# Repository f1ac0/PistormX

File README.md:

# Pistorm'X
If you don't know about Pistorm, the MC68000 CPU replacement using a raspberry Pi, see here : https://github.com/captain-amygdala/pistorm

This PiStorm'X is a simplified CPU board, where all the logic is integrated inside a single CPLD with 5V compatible IOs.

The "Alpha" directory contains the PCB design and CPLD logic files for the first design of the Amiga 500 board and possible mods.

The "Beta" directory shares a second generation of boards for the Amiga 500, Amiga 600 and Amiga 1200. To enjoy both the speed of the PiStorm and the compatibility of the original hardware, they include the ability to disable the Pi and run the original 68k CPU, and the A500 and A600 ones also add 2MB of autoconfig Fast RAM.

Please read the README files there for more info.

# Experimental status
These boards are still experimental, not well tested, and might not work with all system revisions and Pi or 68k software nor provide the same performance or feature than the original. That it works for me does not mean that it will work for you. For this reason you are welcome to assemble your own and share test reports in the discord channel named "beta-testing-pistormx". And for this same reason this board or derivatives must not be sold to end users : do not sell it and do not buy it yet.

- I am an end user, where can I buy it? Buy one of the original PiStorm CPU boards.
- I am a builder, can I sell it? For now, please test it and report your test results.
- I am a maker, can I build derivatives? For now, please test it and report your test results.

# Acknowledgements
The board and its firmware are inspired by the original Pistorm : https://github.com/captain-amygdala/pistorm.
I would like to thank Claude Schwarz for designing and open sourcing the Pistorm and for letting other projects like this one use the name and get inspired by the source code.
Thank you also to EDU_ARANA for letting me use his Pistorm logo with some modifications on the PCB silkscreen.
It is not supported by the PiStorm developers, please don't bother them with issues you might have with it.

# Disclaimer
This is a hobbyist project, it comes with no warranty and no support. Also remember that the Amiga machines are about 30 years old and may fail because of such hardware expansions. Use with caution it could burn your Pi, your Amiga, your house.

I publish my work under the CC-BY-NC-SA license. You may build a board for you or your friend but will not sell or buy it commercially because it is experimental. You must keep the original author's name, source repository (https://github.com/f1ac0/PistormX) and licensing conditions even if you modify the product.

If you find it useful and want to reward my hard work : I am always looking for Amiga/Amstrad CPC and such retro hardware to repair and hack, or software licenses for these. Other than that, give to charities and reduce your carbon footprint.

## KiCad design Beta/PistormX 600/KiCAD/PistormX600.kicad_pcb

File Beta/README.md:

# PiStorm'X Work in progress

NOT ALL DESIGNS IN THIS DIRECTORY ARE TESTED.

If you don't know about PiStorm, the MC68000 CPU replacement using a raspberry Pi, see here : https://github.com/captain-amygdala/pistorm. This PiStorm'X is a simplified CPU board, where all the logic is integrated inside a single CPLD.

# Experimental status
These boards are either experimental, not finished, not yet tested, and might not work for you, have bugs with some system revisions and Pi or 68k software, or have less performance or feature than the original. For this reason you will find here source files only, not fabrication files or ready to use binaries. If you have enough development skills to use them and know what you are doing, you may assemble your own and share test reports in the discord channel named "beta-testing-pistormx". And for this same reason these boards or derivatives must not be sold to end users.

I publish my work under the CC-BY-NC-SA license. You may build a board for you but will not sell or buy it commercially because it is experimental. You must keep the original author's name, source repository (https://github.com/f1ac0/PistormX) and licensing conditions even if you modify the product.

If you find it useful and want to reward my hard work : I am always looking for Amiga/Amstrad CPC/C64 and such retro hardware to repair and hack, or software licenses for these. Other than that, please give to charities and reduce your carbon footprint.

# Acknowledgements
The board and its firmware are inspired by the original PiStorm : https://github.com/captain-amygdala/pistorm.
I would like to thank Claude Schwarz for designing and open sourcing the PiStorm and for letting other projects like this one use the name and get inspired by the source code.
Thank you also to EDU_ARANA for letting me use his PiStorm logo with some modifications on the PCB silkscreen.
It is not supported by the PiStorm developers, please don't bother them with issues you might have with it.

# PiStorm'X 500
The original PiStorm'X project for the Amiga 500 was shared in February 2022. In November 2022, I published the PiStorm'X-68k, a modification to the original project that allow keeping and using the original 68000 by deactivating the PiStorm when needed using a long reset.

This PiStorm'X 500 is an updated board for the Amiga 500 :
- including the PiStorm'X-68k modifications,
- moving the Pi away from the 68000, over the A500 ROM, in order to improve thermal repartition,
- adding 2MB of Fast RAM, which is useful especially during 68000 operation when the Pi is disabled : there was enough room on the two sided board and I believe it is a nice addition to the stock Amiga 500.

/!\ This 1.0 revision board need a patch wire between pin 15 of the 68k header to the pad marked OVR /!\ Do not connect anything else to this pad and check that the BGACK solder jumper is not shorted to the BGACK pin. /!\

The development of this board has been painful. I killed the 7805 Super Fat Agnus of my Rev8a in the development process, because of a dodgy home designed and printed ZIF64 socket that doesn't lock correctly, and an idiot operator that touched the pins without ESD protection. I am looking for an affordable replacement. Then I fought a timing problem caused by the slow transition on the 7MHz clock, because I thought it was a good idea to route it to a global clock pin of the CPLD. It was not - see https://support.xilinx.com/s/article/3226, on the Rev6 with Agnus 8372 318069-02 they are about 25ns, compared to 10ns on my A600 Rev1.5 with Agnus 8375 318069-10 - and this is the reason for the patch wire.

This board is actually working on my A500 Rev6.

# PiStorm'X 600
The PiStorm'X 600 brings the same features as the PiStorm'X 500 to the Amiga 600 : maintain reset during 6 seconds or more to use the 68000, and benefit of 2MB of Fast RAM.

This board is actually working on my A600.

# PiStorm'X 1K2
I have heard about the PiStorm32 for the Amiga 1200 and I wanted to make my own in the Pistorm'X way.

This is not yet finished and untested.

- There are two board layouts : the first board steals the component placement form the PiStorm32-lite ; the second "alt" one offers a more "traditional" design to access the Pi in the trapdoor. Both boards share the same logic but have different CPLD pinout and so will require different bitstreams. With the latter if you don't mind leaving the trapdoor open you may install a standard pin header for the Pi GPIO, leaving the A1200 edge connector as the only special part.
- Since it needs to cope with 32 bits operation with misaligned addresses and dynamic bus sizing, it requires a larger XC95288 CPLD, both in pin count and macrocells.
- This added logic must still be full of bugs and may never work.
- I reused the Pi pinouts from the Pistorm32-lite and since it does not have room for the jtag anymore, the device needs to be programmed externally.
- Even with the same Pi pinouts, it will need updated emulators that does not try to program a FPGA at power up : I hope this will be possible to deactivate it in future upstream releases.
- Like the original PiStorm'X that is not limited by external buffers, it might also be possible to use a faster protocol to speed up chip access a little bit. Or offload some complexity to the emulator to fit inside an even smaller/cheaper CPLD.

For sure this will need some more effort to first make it work !

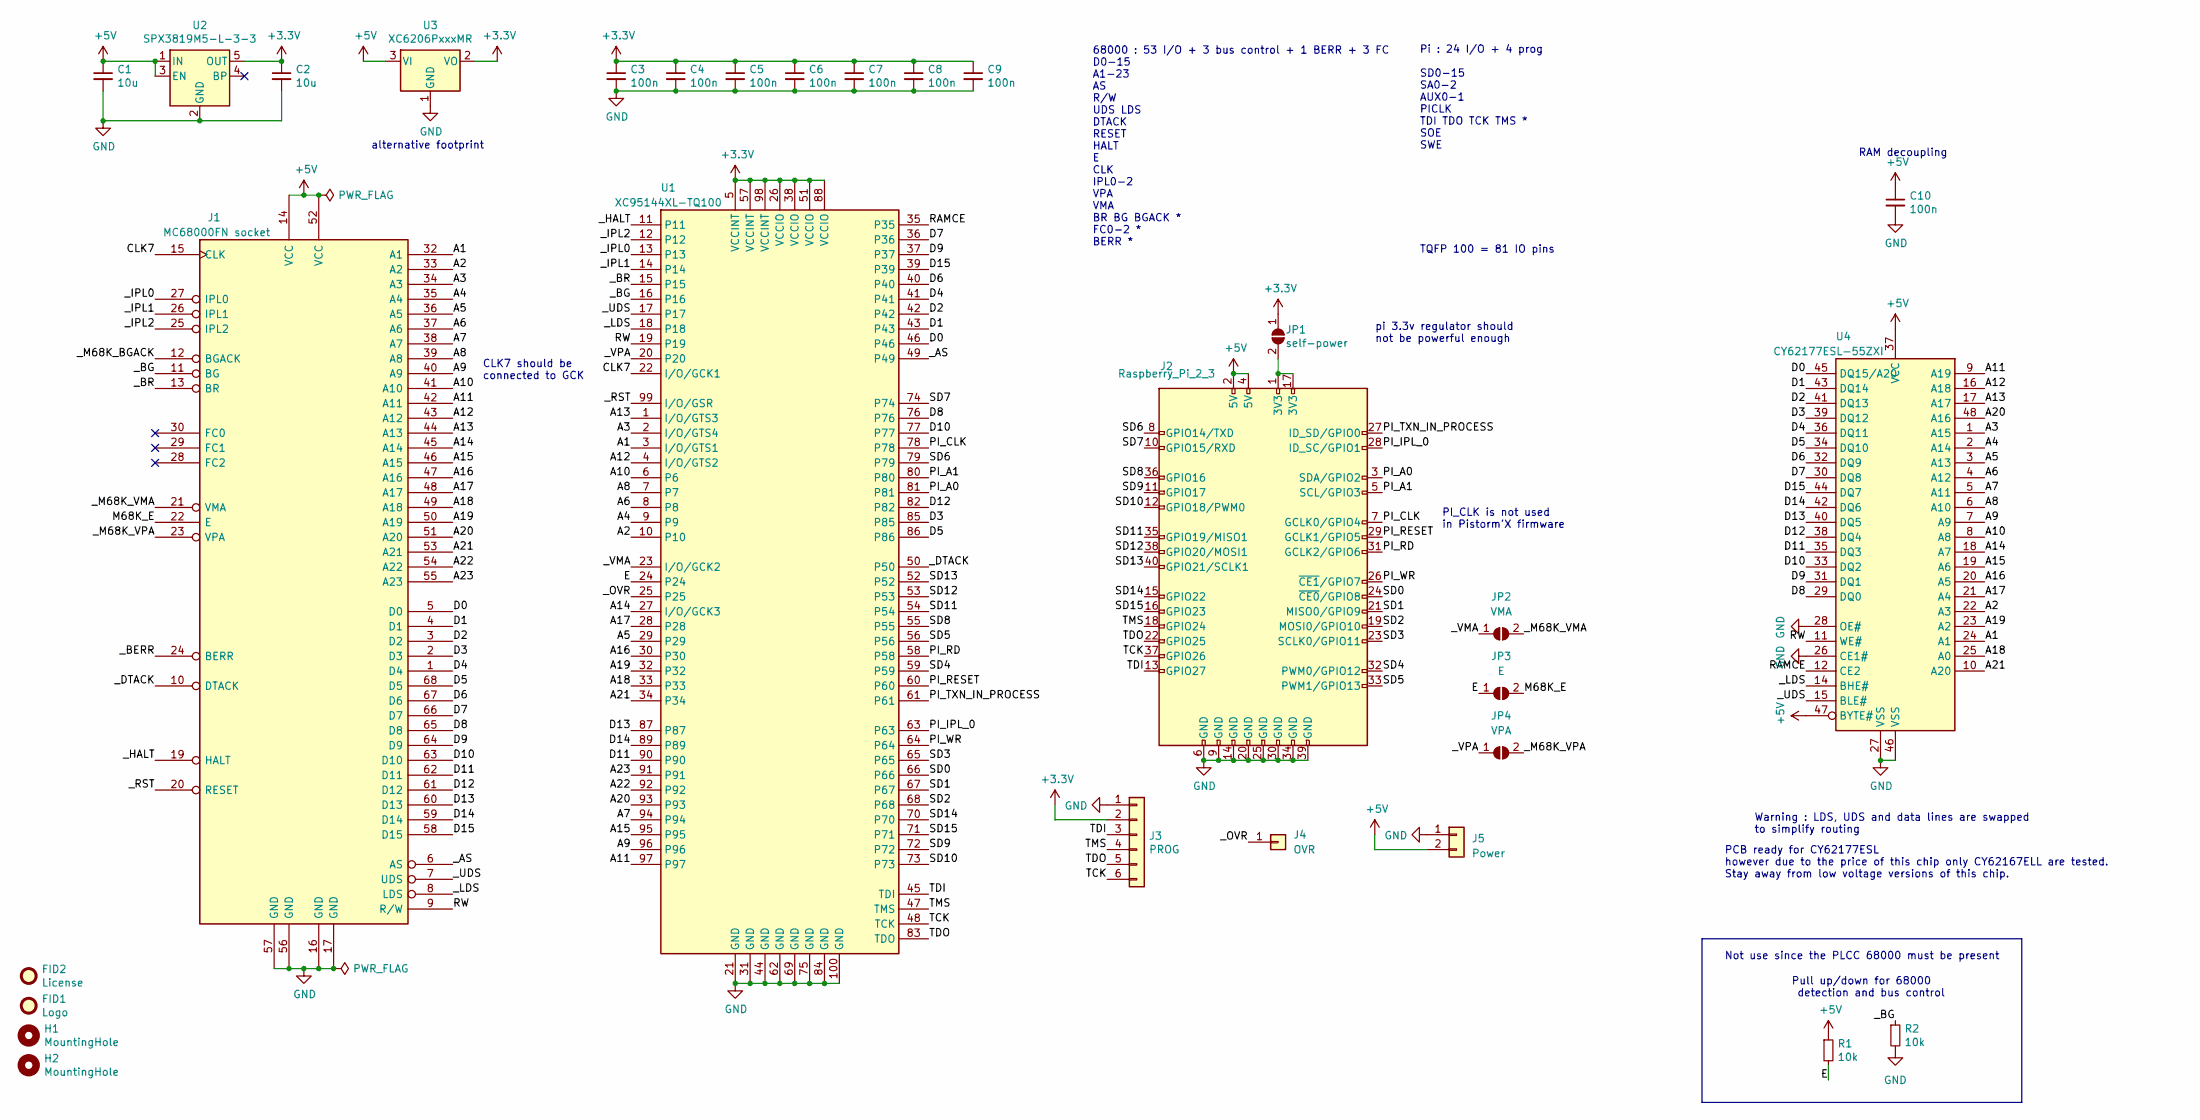
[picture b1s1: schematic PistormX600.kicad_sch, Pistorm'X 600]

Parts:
C1, C2: 10u; C_0805_2012Metric
C3, C4, C5, C6, C7, C8, C9, C10: 100n; C_0805_2012Metric
FID1: Logo; PIC_PistormX_43x10mm
FID2: License; CC_BY_NC_SA_square_silkscreen
H1, H2: MountingHole; MountingHole_2.5mm
J1: MC68000FN socket; PLCC-68_THT-SocketOnTop
J2: Raspberry_Pi_2_3; PinSocket_2x20_P2.54mm_Vertical
J3: PROG; PinHeader_1x06_P2.54mm_Vertical
J4: OVR; PinHeader_1x01_P2.54mm_Vertical
J5: Power; PinHeader_1x02_P2.54mm_Vertical
JP1: self-power; SolderJumper-2_P1.3mm_Open_RoundedPad1.0x1.5mm
JP2: VMA; SolderJumper-2_P1.3mm_Open_RoundedPad1.0x1.5mm
JP3: E; SolderJumper-2_P1.3mm_Open_RoundedPad1.0x1.5mm
JP4: VPA; SolderJumper-2_P1.3mm_Open_RoundedPad1.0x1.5mm
R1, R2: 10k; R_0805_2012Metric
U1: XC95144XL-TQ100; TQFP-100_14x14mm_P0.5mm
U2: SPX3819M5-L-3-3; SOT-23-5
U3: XC6206PxxxMR; SOT-23
U4: CY62177ESL-55ZXI; TSOP-I-48_18.4x12mm_P0.5mm

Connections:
+3.3V: C2.1, C3.1, C4.1, C5.1, C6.1, C7.1, C8.1, C9.1, J3.2, JP1.1 (A), U1.5 (VCCINT), U1.26 (VCCIO), U1.38 (VCCIO), U1.51 (VCCIO), U1.57 (VCCINT), U1.88 (VCCIO), U1.98 (VCCINT), U2.5 (OUT), U3.2 (VO)
+5V: C1.1, C10.1, J1.14 (VCC), J1.52 (VCC), J2.2 (5V), J2.4 (5V), J5.2, R1.1, U2.1 (IN), U2.3 (EN), U3.3 (VI), U4.37 (VCC), U4.47 (BYTE#)
/A1: J1.32 (A1), U1.3 (I/O/GTS1), U4.24 (A1)
/A2: J1.33 (A2), U1.10, U4.22 (A3)
/A3: J1.34 (A3), U1.2 (I/O/GTS4), U4.1 (A15)
/A4: J1.35 (A4), U1.9, U4.2 (A14)
/A5: J1.36 (A5), U1.29, U4.3 (A13)
/A6: J1.37 (A6), U1.8, U4.4 (A12)
/A7: J1.38 (A7), U1.94, U4.5 (A11)
/A8: J1.39 (A8), U1.7, U4.6 (A10)
/A9: J1.40 (A9), U1.96, U4.7 (A9)
/A10: J1.41 (A10), U1.6, U4.8 (A8)
/A11: J1.42 (A11), U1.97, U4.9 (A19)
/A12: J1.43 (A12), U1.4 (I/O/GTS2), U4.16 (A18)
/A13: J1.44 (A13), U1.1 (I/O/GTS3), U4.17 (A17)
/A14: J1.45 (A14), U1.27 (I/O/GCK3), U4.18 (A7)
/A15: J1.46 (A15), U1.95, U4.19 (A6)
/A16: J1.47 (A16), U1.30, U4.20 (A5)
/A17: J1.48 (A17), U1.28, U4.21 (A4)
/A18: J1.49 (A18), U1.33, U4.25 (A0)
/A19: J1.50 (A19), U1.32, U4.23 (A2)
/A20: J1.51 (A20), U1.93, U4.48 (A16)
/A21: J1.53 (A21), U1.34, U4.10 (A20)
/A22: J1.54 (A22), U1.92
/A23: J1.55 (A23), U1.91
/CLK7: J1.15 (CLK), U1.22 (I/O/GCK1)
/D0: J1.5 (D0), U1.46, U4.45 (DQ15/A20)
/D1: J1.4 (D1), U1.43, U4.43 (DQ14)
/D2: J1.3 (D2), U1.42, U4.41 (DQ13)
/D3: J1.2 (D3), U1.85, U4.39 (DQ12)
/D4: J1.1 (D4), U1.41, U4.36 (DQ11)
/D5: J1.68 (D5), U1.86, U4.34 (DQ10)
/D6: J1.67 (D6), U1.40, U4.32 (DQ9)
/D7: J1.66 (D7), U1.36, U4.30 (DQ8)
/D8: J1.65 (D8), U1.76, U4.29 (DQ0)
/D9: J1.64 (D9), U1.37, U4.31 (DQ1)
/D10: J1.63 (D10), U1.77, U4.33 (DQ2)
/D11: J1.62 (D11), U1.90, U4.35 (DQ3)
/D12: J1.61 (D12), U1.82, U4.38 (DQ4)
/D13: J1.60 (D13), U1.87, U4.40 (DQ5)
/D14: J1.59 (D14), U1.89, U4.42 (DQ6)
/D15: J1.58 (D15), U1.39, U4.44 (DQ7)
/E: JP3.1 (A), R1.2, U1.24
/M68K_E: J1.22 (E), JP3.2 (B)
/PI_A0: J2.3 (SDA/GPIO2), U1.81
/PI_A1: J2.5 (SCL/GPIO3), U1.80
/PI_CLK: J2.7 (GCLK0/GPIO4), U1.78
/PI_IPL_0: J2.28 (ID_SC/GPIO1), U1.63
/PI_RD: J2.31 (GCLK2/GPIO6), U1.58
/PI_RESET: J2.29 (GCLK1/GPIO5), U1.60
/PI_TXN_IN_PROCESS: J2.27 (ID_SD/GPIO0), U1.61
/PI_WR: J2.26 (~CE1/GPIO7), U1.64
/RAMCE: U1.35, U4.12 (CE2)
/RW: J1.9 (R/W), U1.19, U4.11 (WE#)
/SD0: J2.24 (~CE0/GPIO8), U1.66
/SD1: J2.21 (MISO0/GPIO9), U1.67
/SD2: J2.19 (MOSI0/GPIO10), U1.68
/SD3: J2.23 (SCLK0/GPIO11), U1.65
/SD4: J2.32 (PWM0/GPIO12), U1.59
/SD5: J2.33 (PWM1/GPIO13), U1.56
/SD6: J2.8 (GPIO14/TXD), U1.79
/SD7: J2.10 (GPIO15/RXD), U1.74
/SD8: J2.36 (GPIO16), U1.55
/SD9: J2.11 (GPIO17), U1.72
/SD10: J2.12 (GPIO18/PWM0), U1.73
/SD11: J2.35 (GPIO19/MISO1), U1.54
/SD12: J2.38 (GPIO20/MOSI1), U1.53
/SD13: J2.40 (GPIO21/SCLK1), U1.52
/SD14: J2.15 (GPIO22), U1.70
/SD15: J2.16 (GPIO23), U1.71
/TCK: J2.37 (GPIO26), J3.6, U1.48 (TCK)
/TDI: J2.13 (GPIO27), J3.3, U1.45 (TDI)
/TDO: J2.22 (GPIO25), J3.5, U1.83 (TDO)
/TMS: J2.18 (GPIO24), J3.4, U1.47 (TMS)
/_AS: J1.6 (AS), U1.49
/_BERR: J1.24 (BERR)
/_BG: J1.11 (BG), R2.1, U1.16
/_BR: J1.13 (BR), U1.15
/_DTACK: J1.10 (DTACK), U1.50
/_HALT: J1.19 (HALT), U1.11
/_IPL0: J1.27 (IPL0), U1.13
/_IPL1: J1.26 (IPL1), U1.14
/_IPL2: J1.25 (IPL2), U1.12
/_LDS: J1.8 (LDS), U1.18, U4.14 (BHE#)
/_M68K_BGACK: J1.12 (BGACK)
/_M68K_VMA: J1.21 (VMA), JP2.2 (B)
/_M68K_VPA: J1.23 (VPA), JP4.2 (B)
/_OVR: J4.1, U1.25
/_RST: J1.20 (RESET), U1.99 (I/O/GSR)
/_UDS: J1.7 (UDS), U1.17, U4.15 (BLE#)
/_VMA: JP2.1 (A), U1.23 (I/O/GCK2)
/_VPA: JP4.1 (A), U1.20
GND: C1.2, C2.2, C3.2, C4.2, C5.2, C6.2, C7.2, C8.2, C9.2, C10.2, J1.16 (GND), J1.17 (GND), J1.56 (GND), J1.57 (GND), J2.6 (GND), J2.9 (GND), J2.14 (GND), J2.20 (GND), J2.25 (GND), J2.30 (GND), J2.34 (GND), J2.39 (GND), J3.1, J5.1, R2.2, U1.21 (GND), U1.31 (GND), U1.44 (GND), U1.62 (GND), U1.69 (GND), U1.75 (GND), U1.84 (GND), U1.100 (GND), U2.2 (GND), U3.1 (GND), U4.26 (CE1#), U4.27 (VSS), U4.28 (OE#), U4.46 (VSS)
unnamed: J2.1 (3V3), J2.17 (3V3), JP1.2 (B)

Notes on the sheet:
CLK7 should be connected to GCK
Pi : 24 I/O + 4 prog SD0-15 SA0-2 AUX0-1 PICLK TDI TDO TCK TMS * SOE SWE
RAM decoupling
PCB ready for CY62177ESL however due to the price of this chip only CY62167ELL are tested. Stay away from low voltage versions of this chip.
Not use since the PLCC 68000 must be present
Pull up/down for 68000 detection and bus control
alternative footprint
pi 3.3v regulator should not be powerful enough
Warning : LDS, UDS and data lines are swapped to simplify routing
TQFP 100 = 81 IO pins
68000 : 53 I/O + 3 bus control + 1 BERR + 3 FC D0-15 A1-23 AS R/W UDS LDS DTACK RESET HALT E CLK IPL0-2 VPA VMA BR BG BGACK * FC0-2 * BERR *
PI_CLK is not used in Pistorm'X firmware

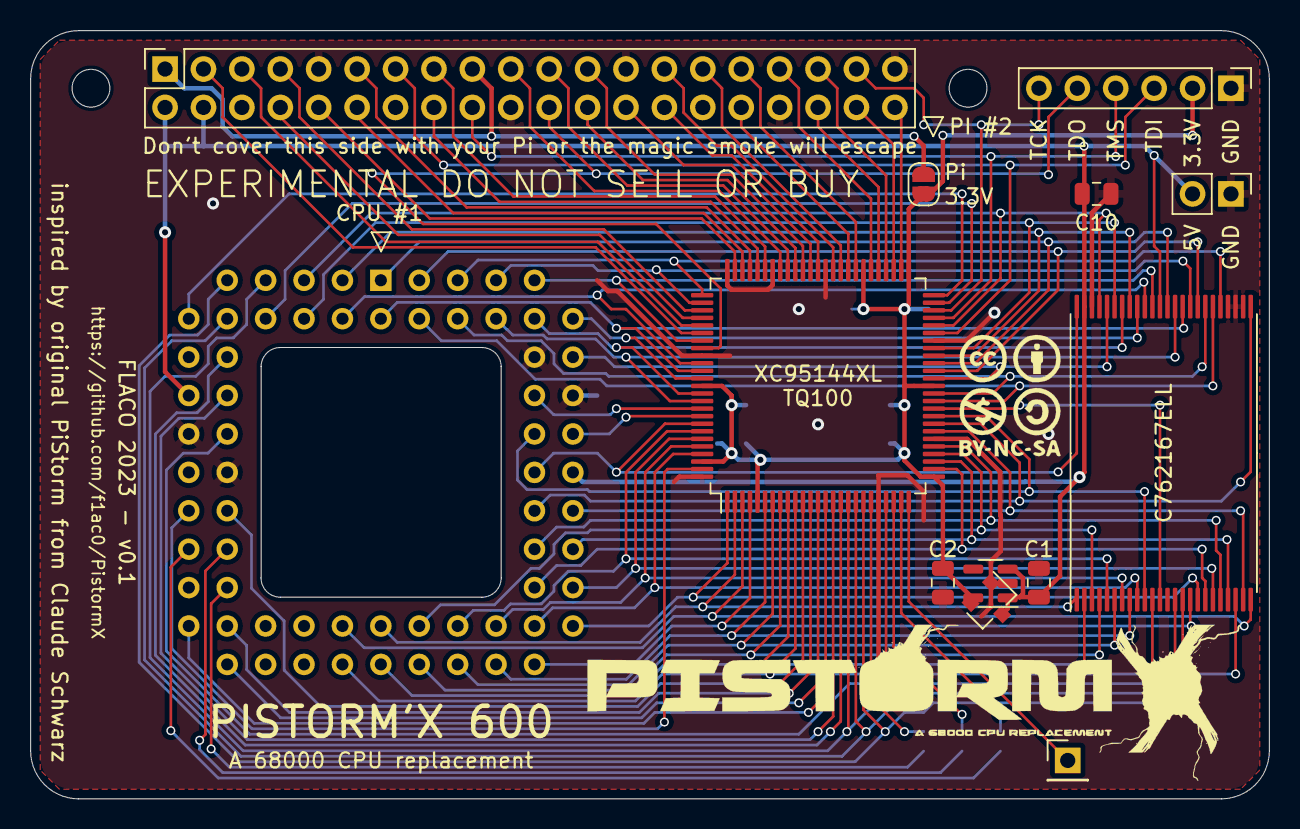
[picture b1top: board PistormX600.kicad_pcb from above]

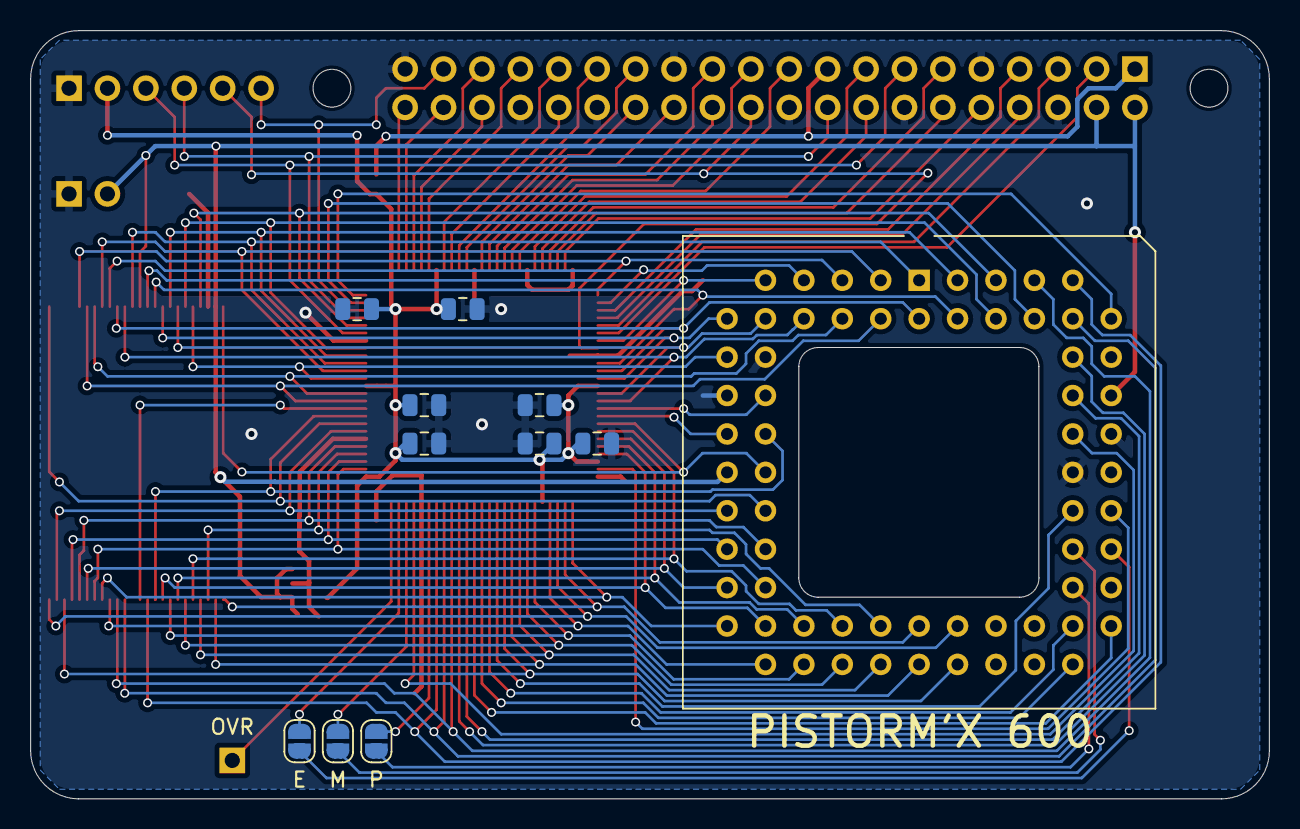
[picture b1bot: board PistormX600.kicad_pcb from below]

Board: 2 copper layers, 81.9 x 50.8 mm, 27 parts (13 on the bottom side), 92 nets.

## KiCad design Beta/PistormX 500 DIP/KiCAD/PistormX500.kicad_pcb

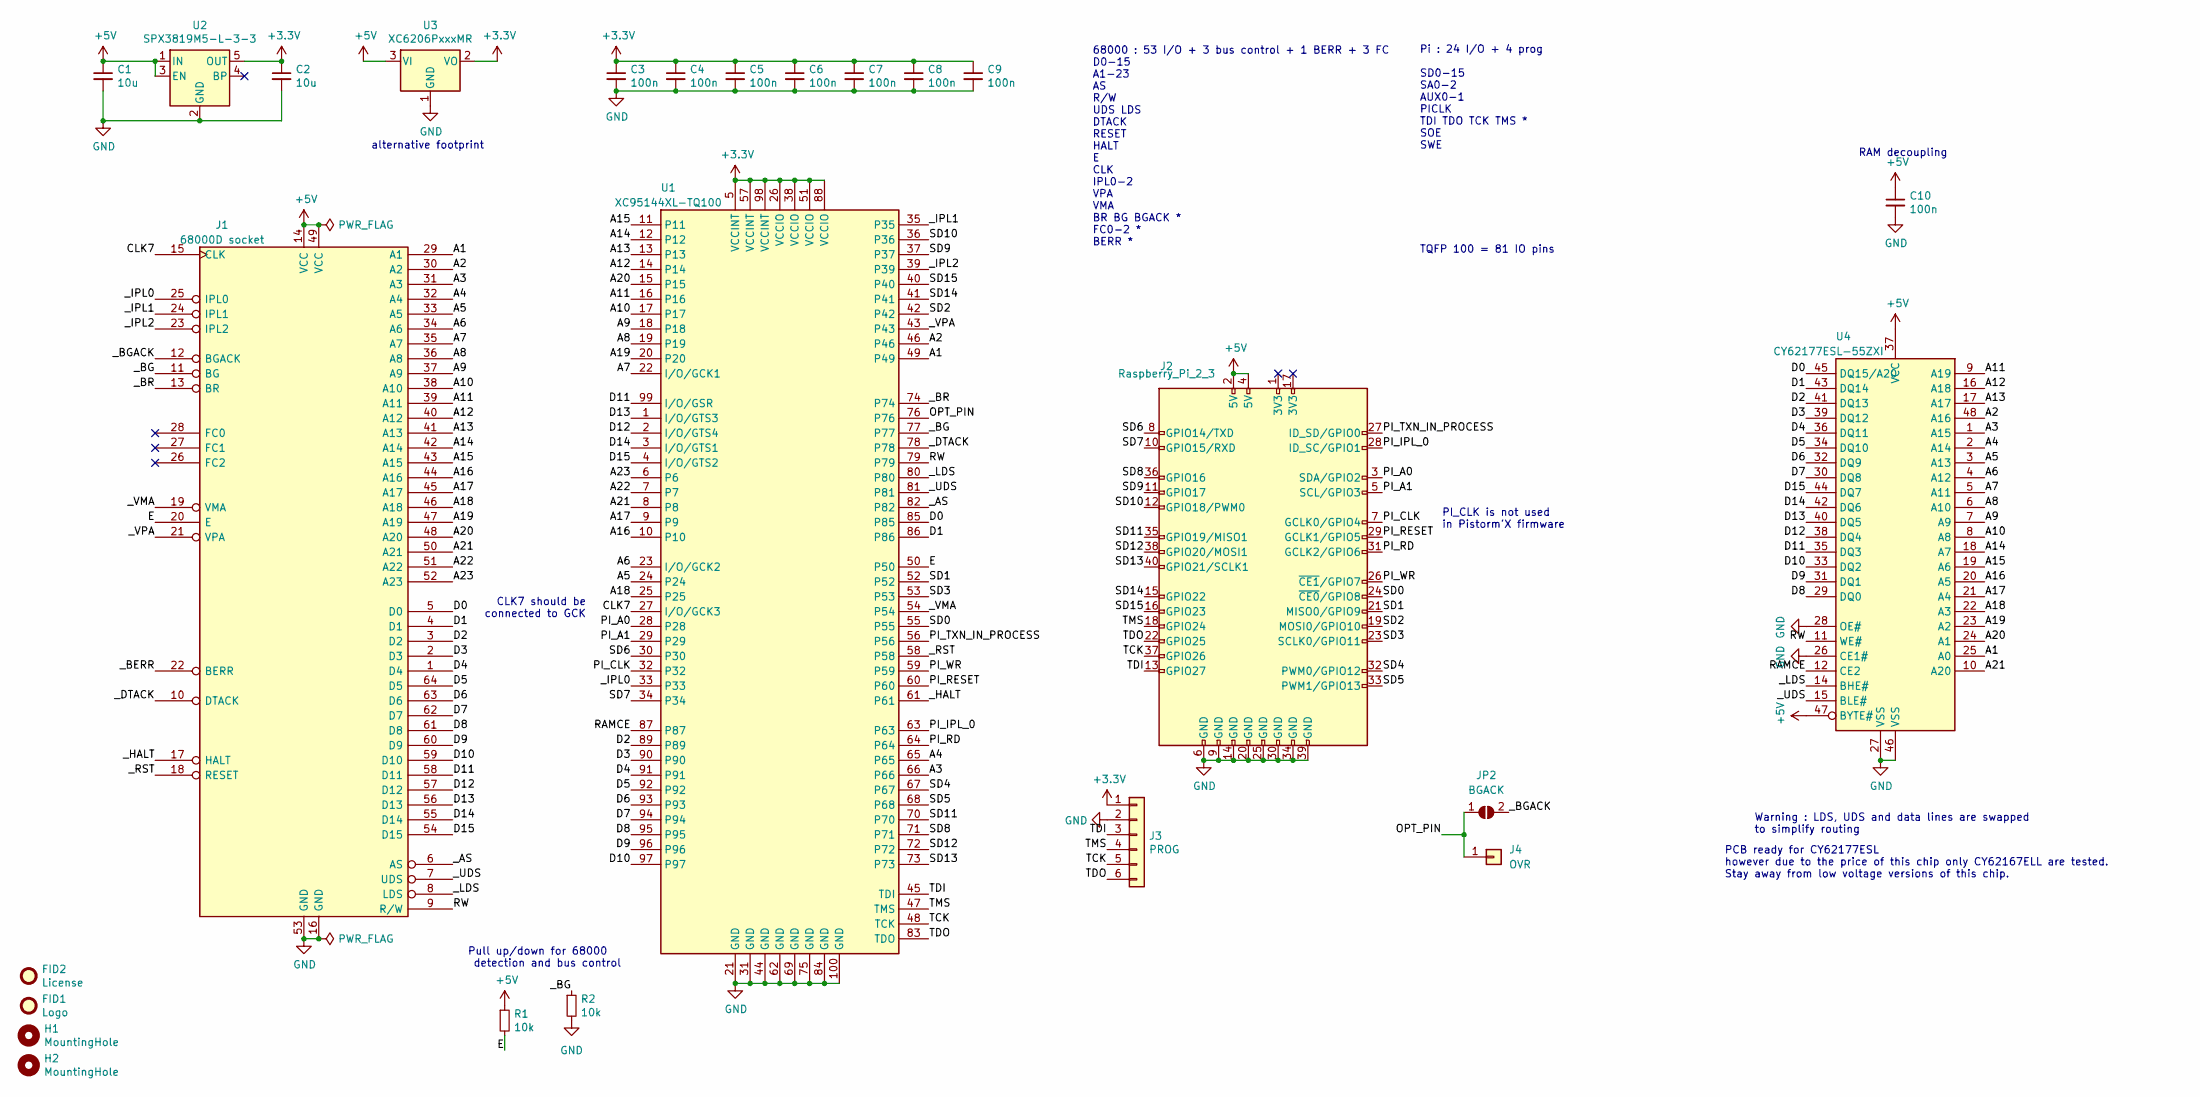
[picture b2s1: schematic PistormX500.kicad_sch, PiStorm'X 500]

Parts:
C1, C2: 10u; C_0805_2012Metric
C3, C4, C5, C6, C7, C8, C9, C10: 100n; C_0805_2012Metric
FID1: Logo; PIC_PistormX_43x10mm
FID2: License; CC_BY_NC_SA_square_silkscreen
H1, H2: MountingHole; MountingHole_2.5mm
J1: 68000D socket; DIP-64_W22.86mm_BigPads1.4
J2: Raspberry_Pi_2_3; PinSocket_2x20_P2.54mm_Vertical
J3: PROG; PinHeader_1x06_P2.54mm_Vertical
J4: OVR; PinHeader_1x01_P2.54mm_Vertical
JP2: BGACK; SolderJumper-2_P1.3mm_Open_RoundedPad1.0x1.5mm
R1, R2: 10k; R_0805_2012Metric
U1: XC95144XL-TQ100; TQFP-100_14x14mm_P0.5mm
U2: SPX3819M5-L-3-3; SOT-23-5
U3: XC6206PxxxMR; SOT-23
U4: CY62177ESL-55ZXI; TSOP-I-48_18.4x12mm_P0.5mm

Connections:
+3.3V: C2.1, C3.1, C4.1, C5.1, C6.1, C7.1, C8.1, C9.1, J3.1, U1.5 (VCCINT), U1.26 (VCCIO), U1.38 (VCCIO), U1.51 (VCCIO), U1.57 (VCCINT), U1.88 (VCCIO), U1.98 (VCCINT), U2.5 (OUT), U3.2 (VO)
+5V: C1.1, C10.1, J1.14 (VCC), J1.49 (VCC), J2.2 (5V), J2.4 (5V), R1.1, U2.1 (IN), U2.3 (EN), U3.3 (VI), U4.37 (VCC), U4.47 (BYTE#)
/A1: J1.29 (A1), U1.49, U4.25 (A0)
/A2: J1.30 (A2), U1.46, U4.48 (A16)
/A3: J1.31 (A3), U1.66, U4.1 (A15)
/A4: J1.32 (A4), U1.65, U4.2 (A14)
/A5: J1.33 (A5), U1.24, U4.3 (A13)
/A6: J1.34 (A6), U1.23 (I/O/GCK2), U4.4 (A12)
/A7: J1.35 (A7), U1.22 (I/O/GCK1), U4.5 (A11)
/A8: J1.36 (A8), U1.19, U4.6 (A10)
/A9: J1.37 (A9), U1.18, U4.7 (A9)
/A10: J1.38 (A10), U1.17, U4.8 (A8)
/A11: J1.39 (A11), U1.16, U4.9 (A19)
/A12: J1.40 (A12), U1.14, U4.16 (A18)
/A13: J1.41 (A13), U1.13, U4.17 (A17)
/A14: J1.42 (A14), U1.12, U4.18 (A7)
/A15: J1.43 (A15), U1.11, U4.19 (A6)
/A16: J1.44 (A16), U1.10, U4.20 (A5)
/A17: J1.45 (A17), U1.9, U4.21 (A4)
/A18: J1.46 (A18), U1.25, U4.22 (A3)
/A19: J1.47 (A19), U1.20, U4.23 (A2)
/A20: J1.48 (A20), U1.15, U4.24 (A1)
/A21: J1.50 (A21), U1.8, U4.10 (A20)
/A22: J1.51 (A22), U1.7
/A23: J1.52 (A23), U1.6
/CLK7: J1.15 (CLK), U1.27 (I/O/GCK3)
/D0: J1.5 (D0), U1.85, U4.45 (DQ15/A20)
/D1: J1.4 (D1), U1.86, U4.43 (DQ14)
/D2: J1.3 (D2), U1.89, U4.41 (DQ13)
/D3: J1.2 (D3), U1.90, U4.39 (DQ12)
/D4: J1.1 (D4), U1.91, U4.36 (DQ11)
/D5: J1.64 (D5), U1.92, U4.34 (DQ10)
/D6: J1.63 (D6), U1.93, U4.32 (DQ9)
/D7: J1.62 (D7), U1.94, U4.30 (DQ8)
/D8: J1.61 (D8), U1.95, U4.29 (DQ0)
/D9: J1.60 (D9), U1.96, U4.31 (DQ1)
/D10: J1.59 (D10), U1.97, U4.33 (DQ2)
/D11: J1.58 (D11), U1.99 (I/O/GSR), U4.35 (DQ3)
/D12: J1.57 (D12), U1.2 (I/O/GTS4), U4.38 (DQ4)
/D13: J1.56 (D13), U1.1 (I/O/GTS3), U4.40 (DQ5)
/D14: J1.55 (D14), U1.3 (I/O/GTS1), U4.42 (DQ6)
/D15: J1.54 (D15), U1.4 (I/O/GTS2), U4.44 (DQ7)
/E: J1.20 (E), R1.2, U1.50
/OPT_PIN: J4.1, JP2.1 (A), U1.76
/PI_A0: J2.3 (SDA/GPIO2), U1.28
/PI_A1: J2.5 (SCL/GPIO3), U1.29
/PI_CLK: J2.7 (GCLK0/GPIO4), U1.32
/PI_IPL_0: J2.28 (ID_SC/GPIO1), U1.63
/PI_RD: J2.31 (GCLK2/GPIO6), U1.64
/PI_RESET: J2.29 (GCLK1/GPIO5), U1.60
/PI_TXN_IN_PROCESS: J2.27 (ID_SD/GPIO0), U1.56
/PI_WR: J2.26 (~CE1/GPIO7), U1.59
/RAMCE: U1.87, U4.12 (CE2)
/RW: J1.9 (R/W), U1.79, U4.11 (WE#)
/SD0: J2.24 (~CE0/GPIO8), U1.55
/SD1: J2.21 (MISO0/GPIO9), U1.52
/SD2: J2.19 (MOSI0/GPIO10), U1.42
/SD3: J2.23 (SCLK0/GPIO11), U1.53
/SD4: J2.32 (PWM0/GPIO12), U1.67
/SD5: J2.33 (PWM1/GPIO13), U1.68
/SD6: J2.8 (GPIO14/TXD), U1.30
/SD7: J2.10 (GPIO15/RXD), U1.34
/SD8: J2.36 (GPIO16), U1.71
/SD9: J2.11 (GPIO17), U1.37
/SD10: J2.12 (GPIO18/PWM0), U1.36
/SD11: J2.35 (GPIO19/MISO1), U1.70
/SD12: J2.38 (GPIO20/MOSI1), U1.72
/SD13: J2.40 (GPIO21/SCLK1), U1.73
/SD14: J2.15 (GPIO22), U1.41
/SD15: J2.16 (GPIO23), U1.40
/TCK: J2.37 (GPIO26), J3.5, U1.48 (TCK)
/TDI: J2.13 (GPIO27), J3.3, U1.45 (TDI)
/TDO: J2.22 (GPIO25), J3.6, U1.83 (TDO)
/TMS: J2.18 (GPIO24), J3.4, U1.47 (TMS)
/_AS: J1.6 (AS), U1.82
/_BERR: J1.22 (BERR)
/_BG: J1.11 (BG), R2.1, U1.77
/_BGACK: J1.12 (BGACK), JP2.2 (B)
/_BR: J1.13 (BR), U1.74
/_DTACK: J1.10 (DTACK), U1.78
/_HALT: J1.17 (HALT), U1.61
/_IPL0: J1.25 (IPL0), U1.33
/_IPL1: J1.24 (IPL1), U1.35
/_IPL2: J1.23 (IPL2), U1.39
/_LDS: J1.8 (LDS), U1.80, U4.14 (BHE#)
/_RST: J1.18 (RESET), U1.58
/_UDS: J1.7 (UDS), U1.81, U4.15 (BLE#)
/_VMA: J1.19 (VMA), U1.54
/_VPA: J1.21 (VPA), U1.43
GND: C1.2, C2.2, C3.2, C4.2, C5.2, C6.2, C7.2, C8.2, C9.2, C10.2, J1.16 (GND), J1.53 (GND), J2.6 (GND), J2.9 (GND), J2.14 (GND), J2.20 (GND), J2.25 (GND), J2.30 (GND), J2.34 (GND), J2.39 (GND), J3.2, R2.2, U1.21 (GND), U1.31 (GND), U1.44 (GND), U1.62 (GND), U1.69 (GND), U1.75 (GND), U1.84 (GND), U1.100 (GND), U2.2 (GND), U3.1 (GND), U4.26 (CE1#), U4.27 (VSS), U4.28 (OE#), U4.46 (VSS)

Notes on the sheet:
CLK7 should be connected to GCK
Pi : 24 I/O + 4 prog SD0-15 SA0-2 AUX0-1 PICLK TDI TDO TCK TMS * SOE SWE
PCB ready for CY62177ESL however due to the price of this chip only CY62167ELL are tested. Stay away from low voltage versions of this chip.
Pull up/down for 68000 detection and bus control
alternative footprint
Warning : LDS, UDS and data lines are swapped to simplify routing
TQFP 100 = 81 IO pins
68000 : 53 I/O + 3 bus control + 1 BERR + 3 FC D0-15 A1-23 AS R/W UDS LDS DTACK RESET HALT E CLK IPL0-2 VPA VMA BR BG BGACK * FC0-2 * BERR *
RAM decoupling
PI_CLK is not used in Pistorm'X firmware

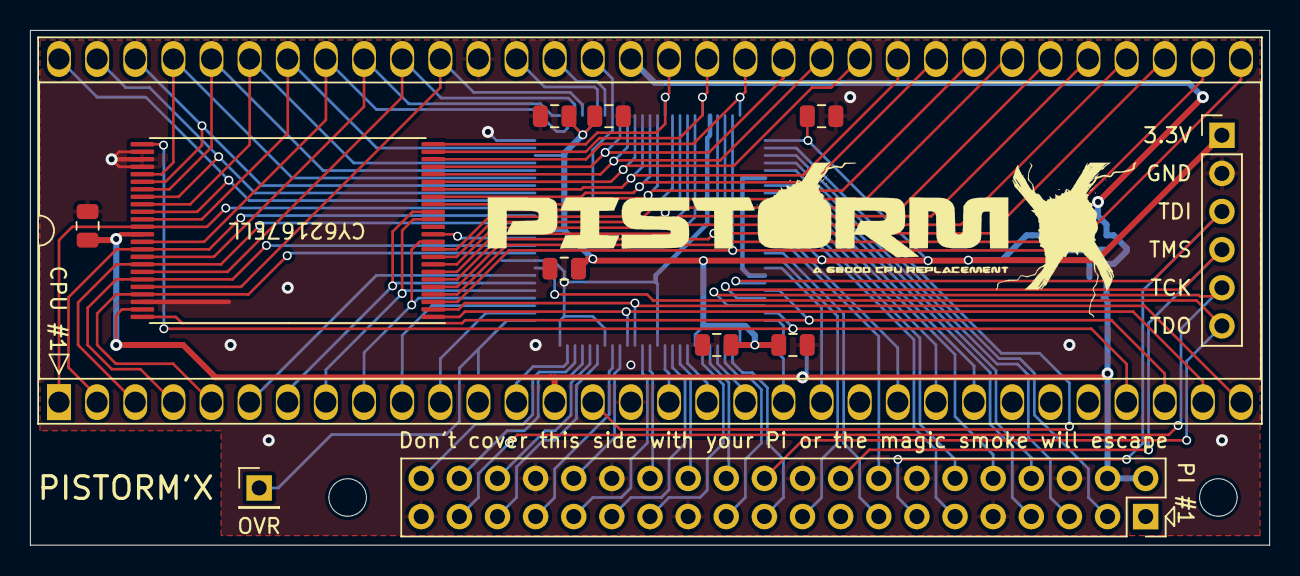
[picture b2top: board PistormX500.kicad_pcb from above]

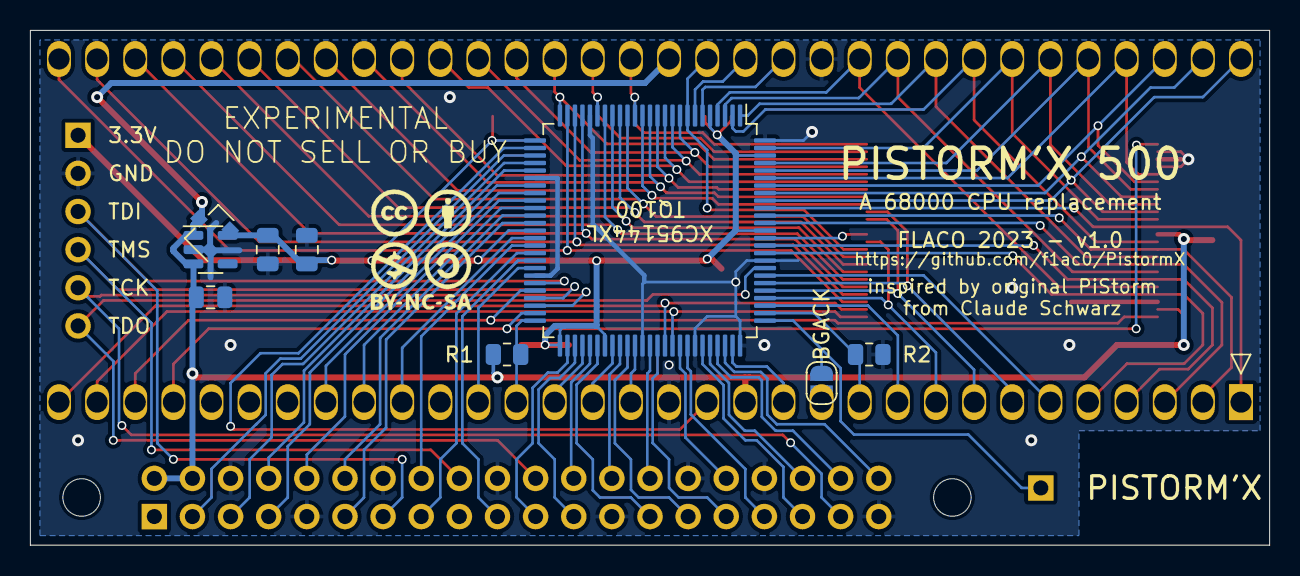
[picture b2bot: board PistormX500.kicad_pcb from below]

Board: 2 copper layers, 82.6 x 34.3 mm, 25 parts (10 on the bottom side), 89 nets.
